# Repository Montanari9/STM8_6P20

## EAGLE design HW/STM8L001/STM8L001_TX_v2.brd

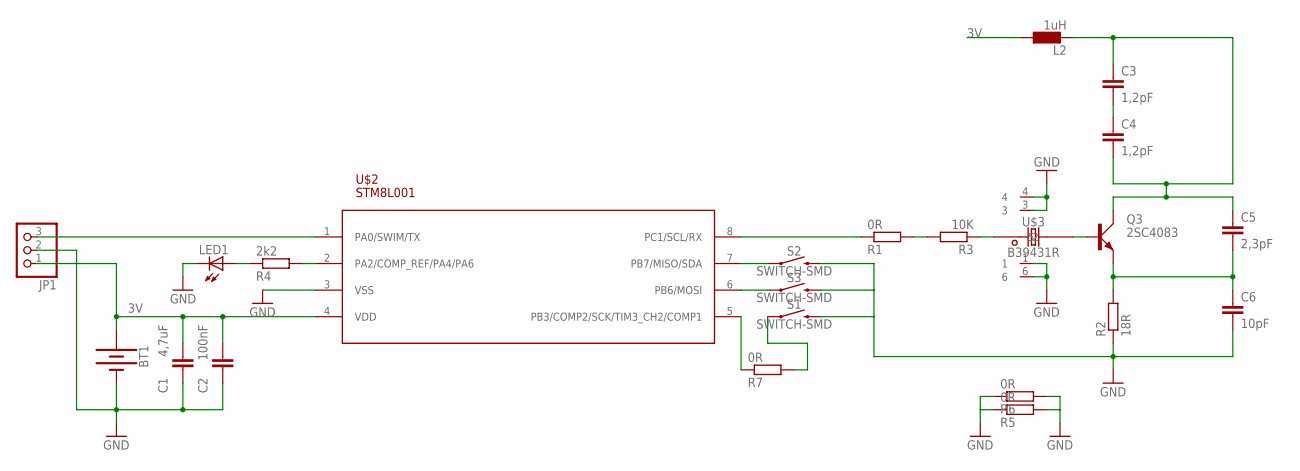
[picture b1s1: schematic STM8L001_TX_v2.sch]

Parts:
BT1: BATTERY-20MM_PTH; BATTCOM_20MM_PTH
C1: 4,7uF; C0603
C2: 100nF; C0603
C3, C4: 1,2pF; C0402
C5: 2,3pF; C0402
C6: 10pF; C0402
JP1: PINHD-1X3; 1X03
L2: 1uH; L3230M
LED1: LED_ESML0603; LED_SML0603
Q3: 2SC4083; UMT3
R1, R5, R6, R7: 0R; R1206
R2: 18R; R0402
R3: 10K; R0402
R4: 2k2; R1206
S1, S2, S3: SWITCH-SMD; TACTILE_SWITCH_SMD_6.0X3.5MM
U$2: STM8L001; SO08
U$3: B39431R; SON120P300X300X110-6N

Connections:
3V: BT1.1 (+), C1.2, C2.2, JP1.1, L2.1, U$2.4 (VDD)
GND: BT1.2 (-), C1.1, C2.1, C6.2, JP1.2, LED1.C, R2.1, R5.1, R5.2, R6.1, R6.2, S1.2, S2.2, S3.2, U$2.3 (VSS), U$3.1, U$3.3, U$3.4, U$3.6
unnamed: R3.1, U$3.2
unnamed: C3.1, C4.2, C5.1, L2.2, Q3.3 (C)
unnamed: R4.2, U$2.2 (PA2/COMP_REF/PA4/PA6)
unnamed: S3.1, U$2.6 (PB6/MOSI)
unnamed: C5.2, C6.1, Q3.1 (E), R2.2
unnamed: LED1.A, R4.1
unnamed: C3.2, C4.1
unnamed: JP1.3, U$2.1 (PA0/SWIM/TX)
unnamed: S2.1, U$2.7 (PB7/MISO/SDA)
unnamed: R1.2, R3.2
unnamed: R7.2, S1.1
unnamed: R1.1, U$2.8 (PC1/SCL/RX)
unnamed: R7.1, U$2.5 (PB3/COMP2/SCK/TIM3_CH2/COMP1)
unnamed: Q3.2 (B), U$3.5

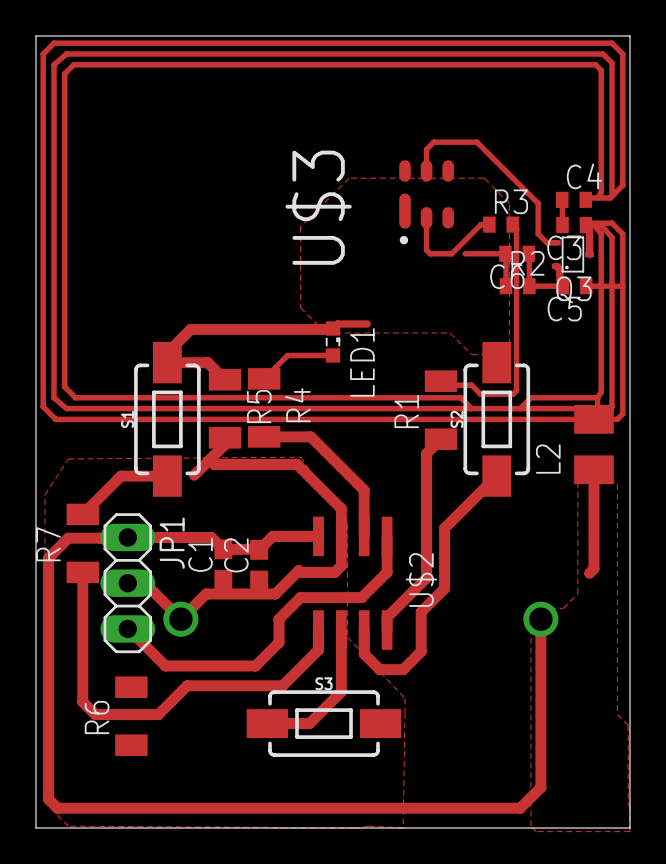
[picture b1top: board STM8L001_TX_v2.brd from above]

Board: 2 copper layers, 33.0 x 44.0 mm, 23 parts (1 on the bottom side), 16 nets.

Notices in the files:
parts and their libraries:
SparkFun-Switches: Licensing: Creative Commons ShareAlike 4.0 International - https://creativecommons.org/licenses/by-sa/4.0
